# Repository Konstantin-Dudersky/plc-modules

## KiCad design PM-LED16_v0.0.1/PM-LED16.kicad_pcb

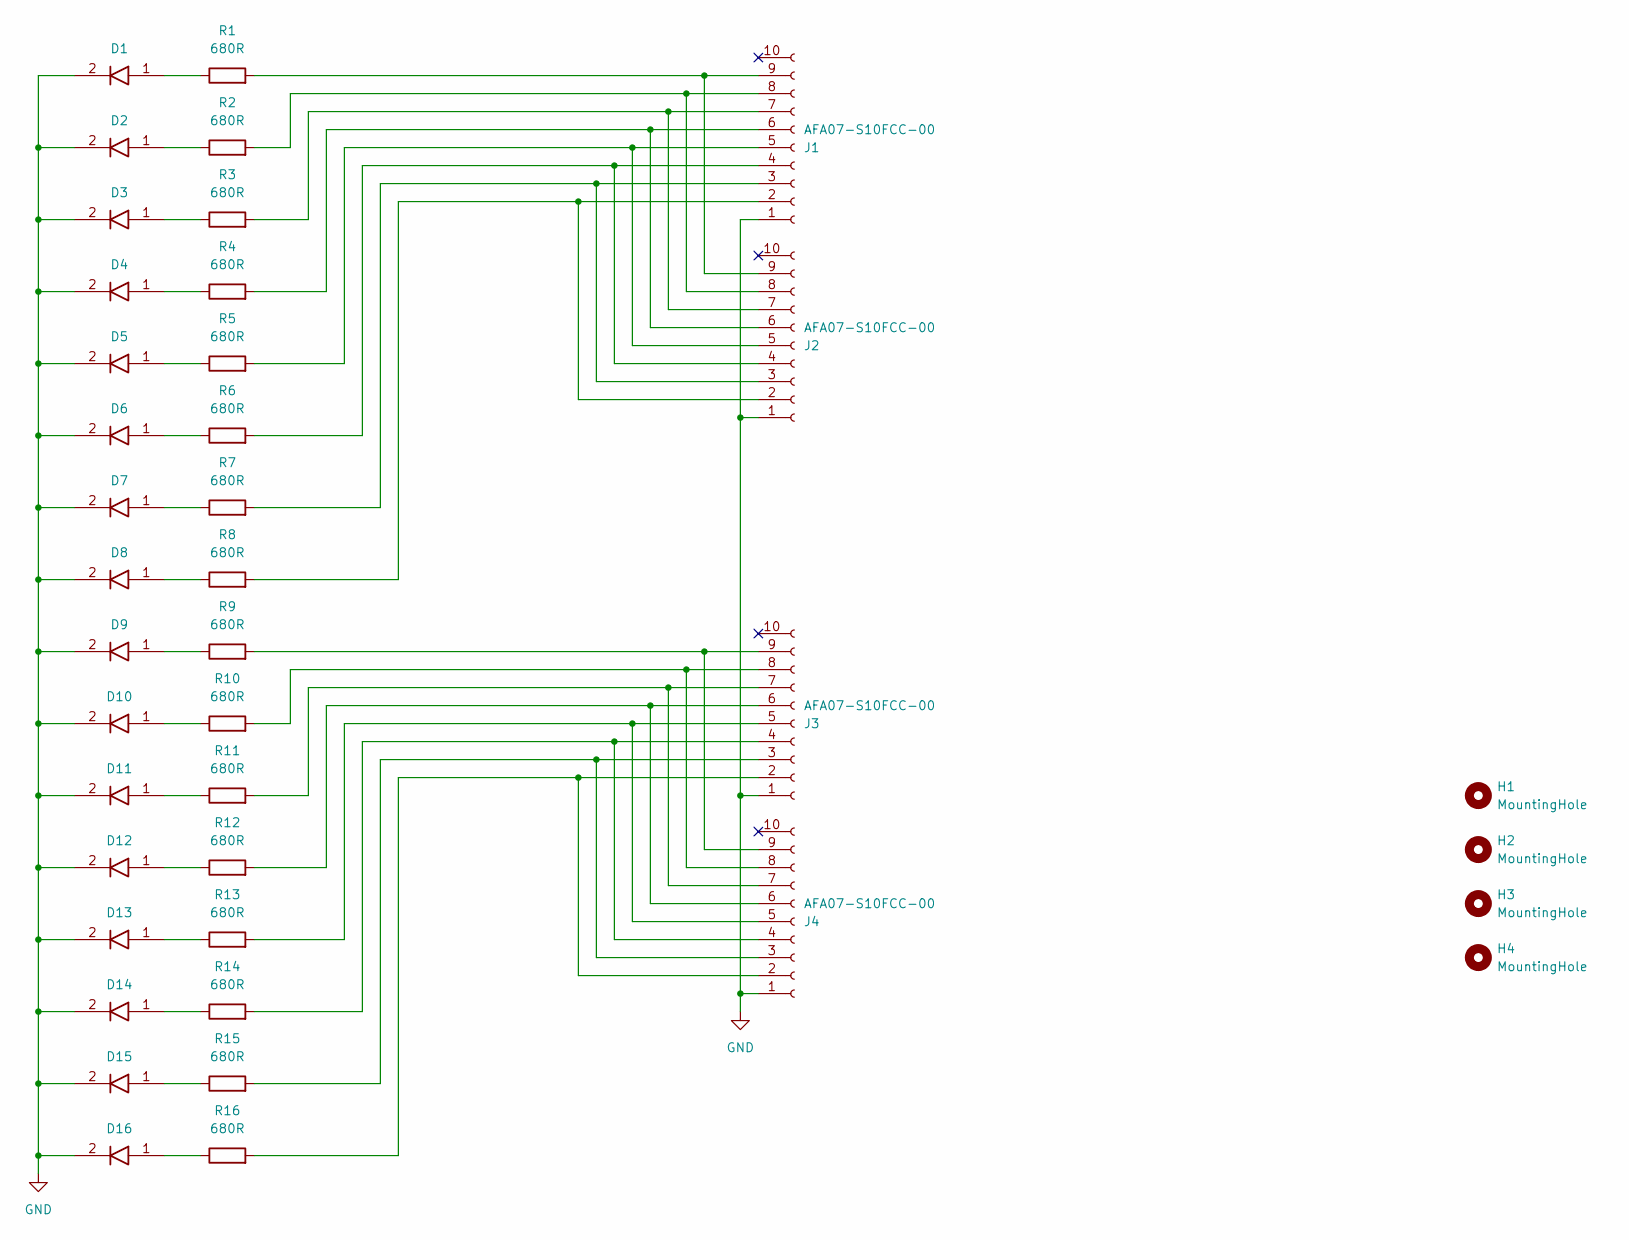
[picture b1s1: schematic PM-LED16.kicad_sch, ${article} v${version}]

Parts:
D1, D2, D3, D4, D5, D6, D7, D8, D9, D10, D11, D12, D13, D14, D15, D16: 12-21_GHC-YR2S2_2C; 1221GHCYR2S22C; part_ipn 12-21/GHC-YR2S2/2C
H1, H2, H3, H4: MountingHole; MountingHole_2.2mm_M2
J1, J2, J3, J4: AFA07-S10FCC-00; CONN10_AFA07-S10_JUS
R1, R2, R3, R4, R5, R6, R7, R8, R9, R10, R11, R12, R13, R14, R15, R16: 680R; R_1206_3216Metric_Pad1.30x1.75mm_HandSolder; part_ipn R_680R_1206_1%

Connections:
GND: D1.2, D2.2, D3.2, D4.2, D5.2, D6.2, D7.2, D8.2, D9.2, D10.2, D11.2, D12.2, D13.2, D14.2, D15.2, D16.2, J1.1, J2.1, J3.1, J4.1
unnamed: D1.1, R1.1
unnamed: D2.1, R2.1
unnamed: D3.1, R3.1
unnamed: D4.1, R4.1
unnamed: D5.1, R5.1
unnamed: D6.1, R6.1
unnamed: D7.1, R7.1
unnamed: D8.1, R8.1
unnamed: D9.1, R9.1
unnamed: D10.1, R10.1
unnamed: D11.1, R11.1
unnamed: D12.1, R12.1
unnamed: D13.1, R13.1
unnamed: D14.1, R14.1
unnamed: D15.1, R15.1
unnamed: D16.1, R16.1
unnamed: J1.2, J2.2, R8.2
unnamed: J1.3, J2.3, R7.2
unnamed: J1.4, J2.4, R6.2
unnamed: J1.5, J2.5, R5.2
unnamed: J1.6, J2.6, R4.2
unnamed: J1.7, J2.7, R3.2
unnamed: J1.8, J2.8, R2.2
unnamed: J1.9, J2.9, R1.2
unnamed: J3.2, J4.2, R16.2
unnamed: J3.3, J4.3, R15.2
unnamed: J3.4, J4.4, R14.2
unnamed: J3.5, J4.5, R13.2
unnamed: J3.6, J4.6, R12.2
unnamed: J3.7, J4.7, R11.2
unnamed: J3.8, J4.8, R10.2
unnamed: J3.9, J4.9, R9.2

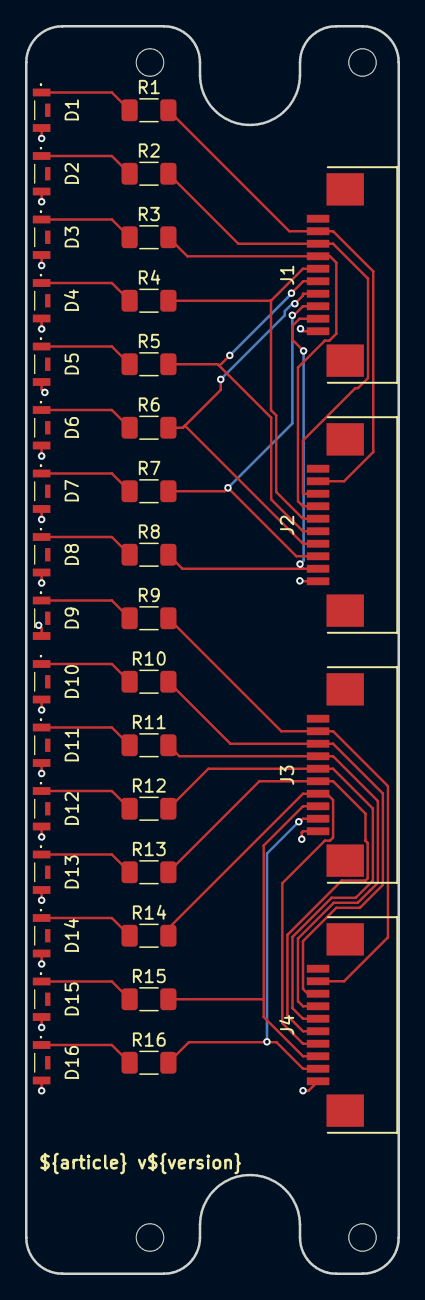
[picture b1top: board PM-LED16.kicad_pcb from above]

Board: 2 copper layers, 29.8 x 99.8 mm, 41 parts (1 on the bottom side), 33 nets.

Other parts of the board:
Logo_kicad: KiCad-Logo2_5mm_SilkScreen

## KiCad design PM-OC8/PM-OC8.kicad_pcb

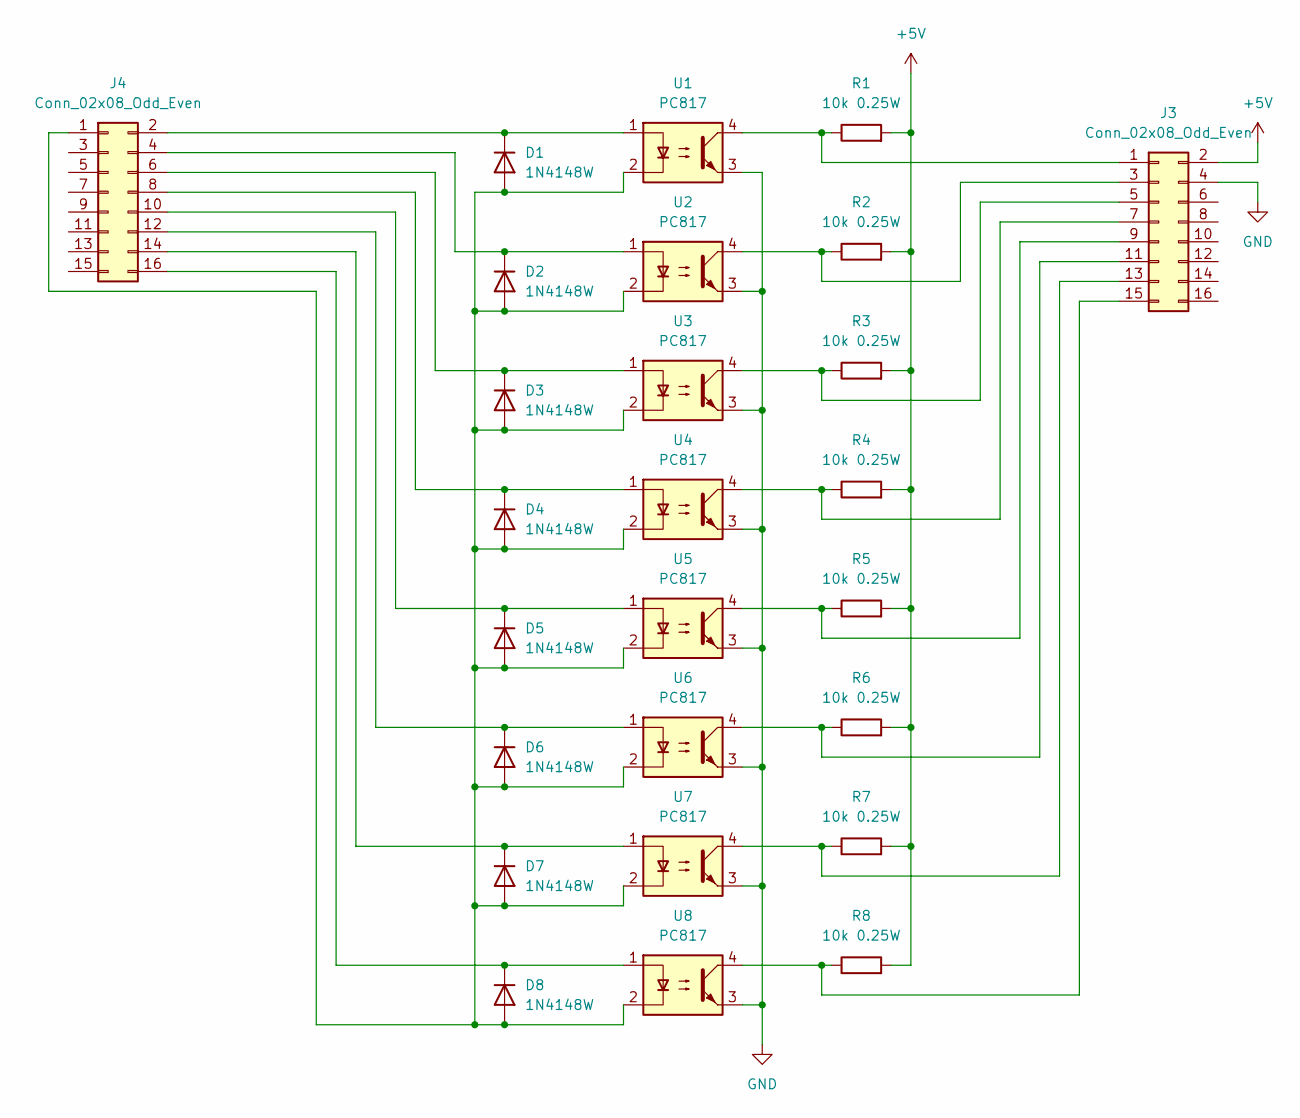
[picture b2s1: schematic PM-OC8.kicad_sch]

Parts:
D1, D2, D3, D4, D5, D6, D7, D8: 1N4148W; D_SOD-123; MfrPart 1N4148W
J3, J4: Conn_02x08_Odd_Even; PinHeader_2x08_P2.54mm_Vertical_SMD
R1, R2, R3, R4, R5, R6, R7, R8: 10k 0.25W; R_1206_3216Metric_Pad1.30x1.75mm_HandSolder
U1, U2, U3, U4, U5, U6, U7, U8: PC817; SOP-4_3.8x4.1mm_P2.54mm

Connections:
+5V: J3.2, R1.2, R2.2, R3.2, R4.2, R5.2, R6.2, R7.2, R8.2
GND: J3.4, U1.3, U2.3, U3.3, U4.3, U5.3, U6.3, U7.3, U8.3
unnamed: D1.2 (A), D2.2 (A), D3.2 (A), D4.2 (A), D5.2 (A), D6.2 (A), D7.2 (A), D8.2 (A), J4.1, U1.2, U2.2, U3.2, U4.2, U5.2, U6.2, U7.2, U8.2
unnamed: D1.1 (K), J4.2, U1.1
unnamed: D2.1 (K), J4.4, U2.1
unnamed: D3.1 (K), J4.6, U3.1
unnamed: D4.1 (K), J4.8, U4.1
unnamed: D5.1 (K), J4.10, U5.1
unnamed: D6.1 (K), J4.12, U6.1
unnamed: D7.1 (K), J4.14, U7.1
unnamed: D8.1 (K), J4.16, U8.1
unnamed: J3.1, R1.1, U1.4
unnamed: J3.3, R2.1, U2.4
unnamed: J3.5, R3.1, U3.4
unnamed: J3.7, R4.1, U4.4
unnamed: J3.9, R5.1, U5.4
unnamed: J3.11, R6.1, U6.4
unnamed: J3.13, R7.1, U7.4
unnamed: J3.15, R8.1, U8.4

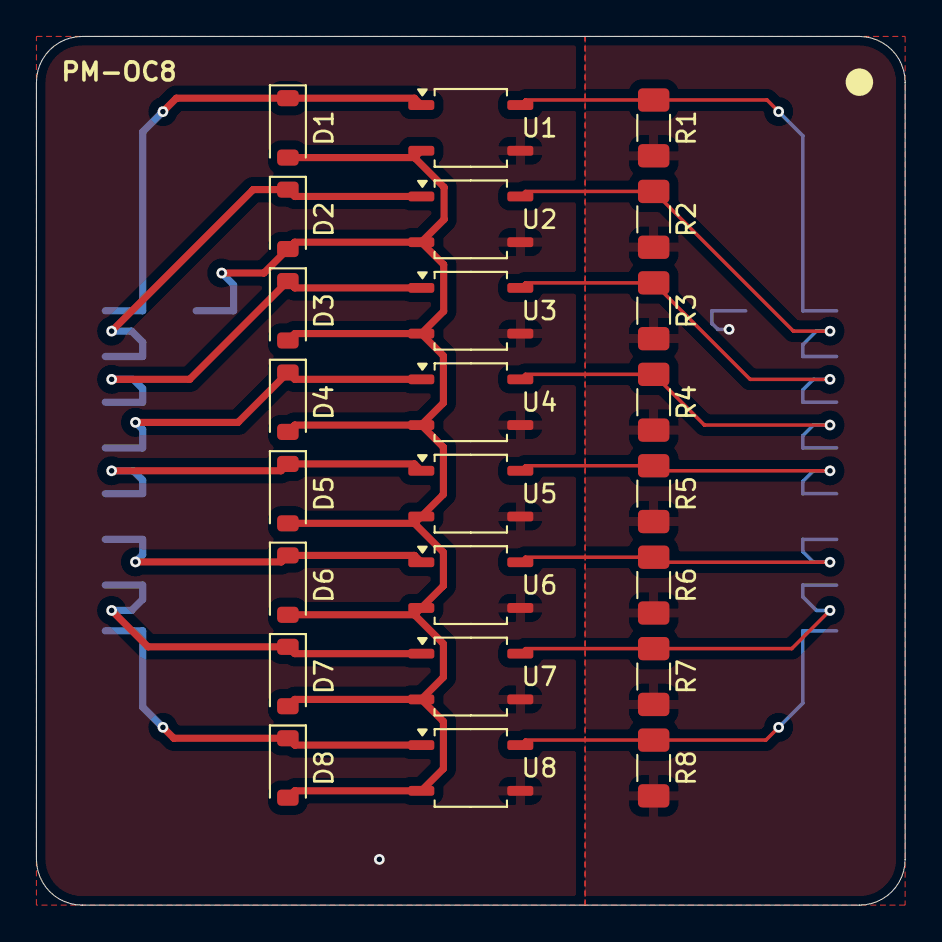
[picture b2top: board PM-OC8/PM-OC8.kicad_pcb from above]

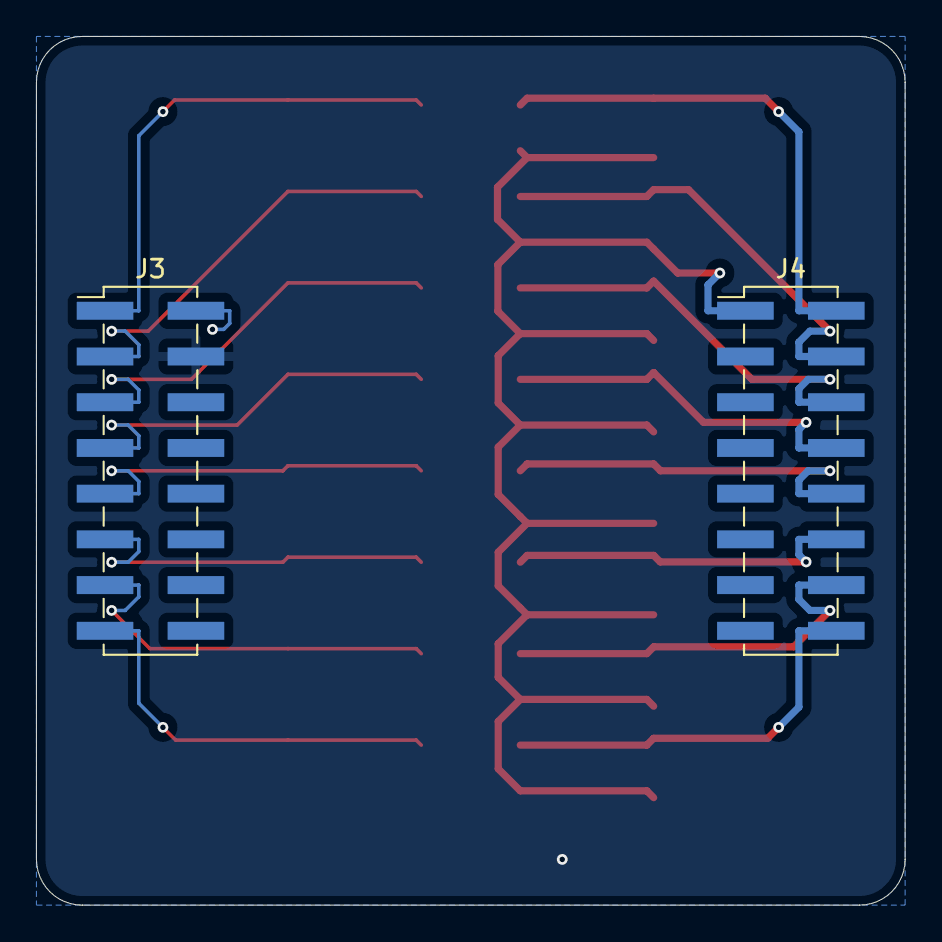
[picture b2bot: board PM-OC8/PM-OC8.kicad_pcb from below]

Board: 2 copper layers, 48.3 x 48.3 mm, 26 parts (2 on the bottom side), 19 nets.

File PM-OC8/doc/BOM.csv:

Reference,Value,Footprint,Qty,NextPCB_price,NextPCB_url
"D1,D2,D3,D4,D5,D6,D7,D8",1N4148W,Diode_SMD:D_SOD-123,8,0.00811,https://www.hqonline.com/product-detail/switching-diodes--sm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
"J3,J4",Conn_02x08_Odd_Even,Connector_PinHeader_2.54mm:PinHeader_2x08_P2.54mm_Vertical_SMD,2,,
"R1,R2,R3,R4,R5,R6,R7,R8",10k 0.25W,Resistor_SMD:R_1206_3216Metric_Pad1.30x1.75mm_HandSolder,8,0.00233,https://www.hqonline.com/product-detail/chip-resistors-yageo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
"U1,U2,U3,U4,U5,U6,U7,U8",PC817,Package_SO:SOP-4_3.8x4.1mm_P2.54mm,8,0.03334,https://www.hqonline.com/product-detail/photocouplers-slkor-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

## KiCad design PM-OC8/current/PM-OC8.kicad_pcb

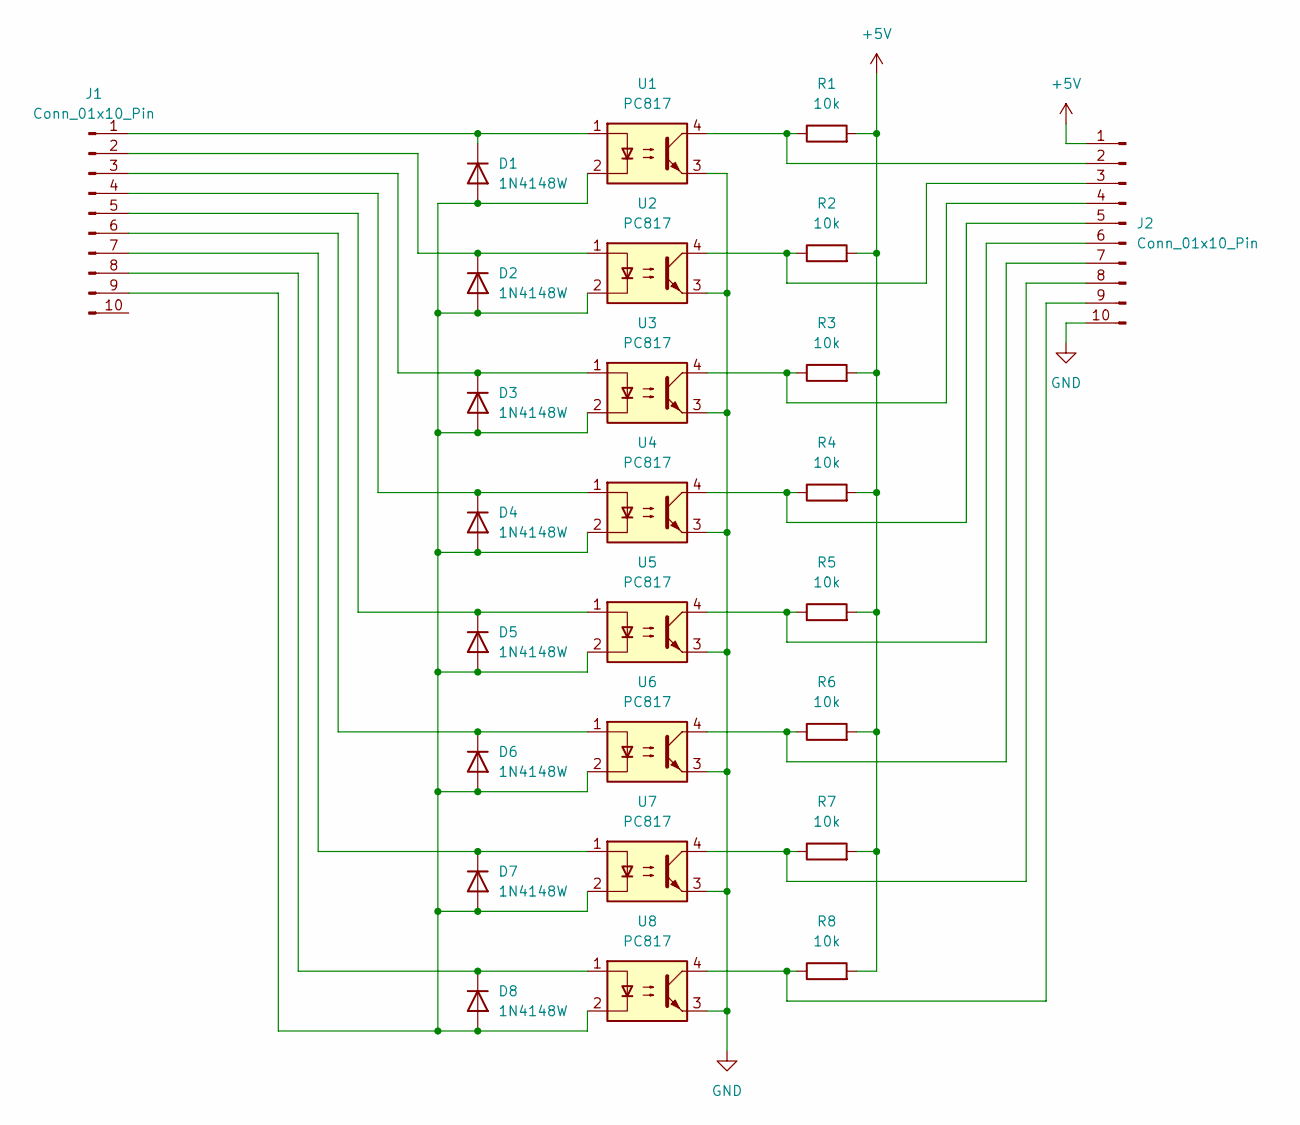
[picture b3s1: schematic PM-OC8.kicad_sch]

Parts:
D1, D2, D3, D4, D5, D6, D7, D8: 1N4148W; D_SOD-123
J1, J2: Conn_01x10_Pin; PinHeader_1x10_P2.54mm_Vertical_SMD_Pin1Left
R1, R2, R3, R4, R5, R6, R7, R8: 10k; R_1206_3216Metric_Pad1.30x1.75mm_HandSolder
U1, U2, U3, U4, U5, U6, U7, U8: PC817; SOP-4_3.8x4.1mm_P2.54mm

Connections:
+5V: J2.1, R1.2, R2.2, R3.2, R4.2, R5.2, R6.2, R7.2, R8.2
GND: J2.10, U1.3, U2.3, U3.3, U4.3, U5.3, U6.3, U7.3, U8.3
unnamed: D1.2 (A), D2.2 (A), D3.2 (A), D4.2 (A), D5.2 (A), D6.2 (A), D7.2 (A), D8.2 (A), J1.9, U1.2, U2.2, U3.2, U4.2, U5.2, U6.2, U7.2, U8.2
unnamed: D1.1 (K), J1.1, U1.1
unnamed: D2.1 (K), J1.2, U2.1
unnamed: D3.1 (K), J1.3, U3.1
unnamed: D4.1 (K), J1.4, U4.1
unnamed: D5.1 (K), J1.5, U5.1
unnamed: D6.1 (K), J1.6, U6.1
unnamed: D7.1 (K), J1.7, U7.1
unnamed: D8.1 (K), J1.8, U8.1
unnamed: J2.2, R1.1, U1.4
unnamed: J2.3, R2.1, U2.4
unnamed: J2.4, R3.1, U3.4
unnamed: J2.5, R4.1, U4.4
unnamed: J2.6, R5.1, U5.4
unnamed: J2.7, R6.1, U6.4
unnamed: J2.8, R7.1, U7.4
unnamed: J2.9, R8.1, U8.4

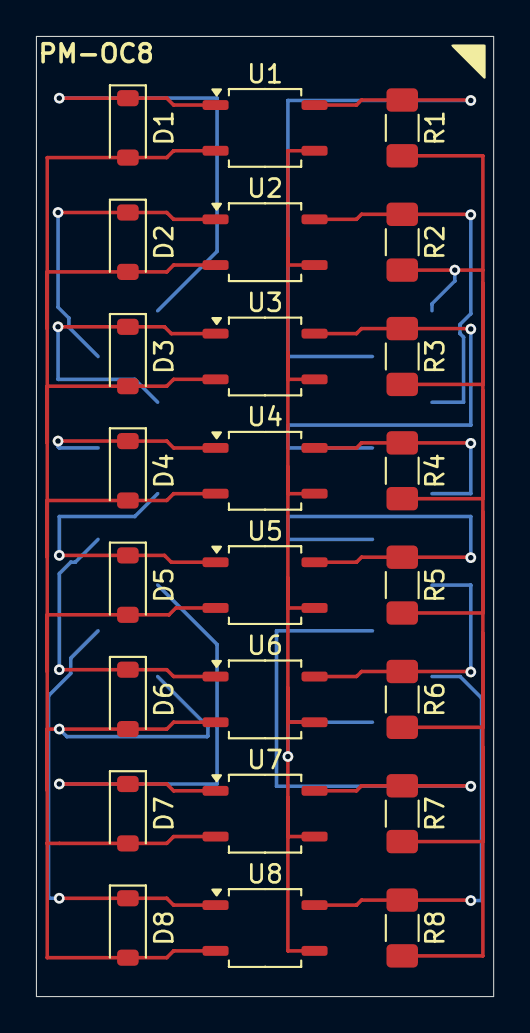
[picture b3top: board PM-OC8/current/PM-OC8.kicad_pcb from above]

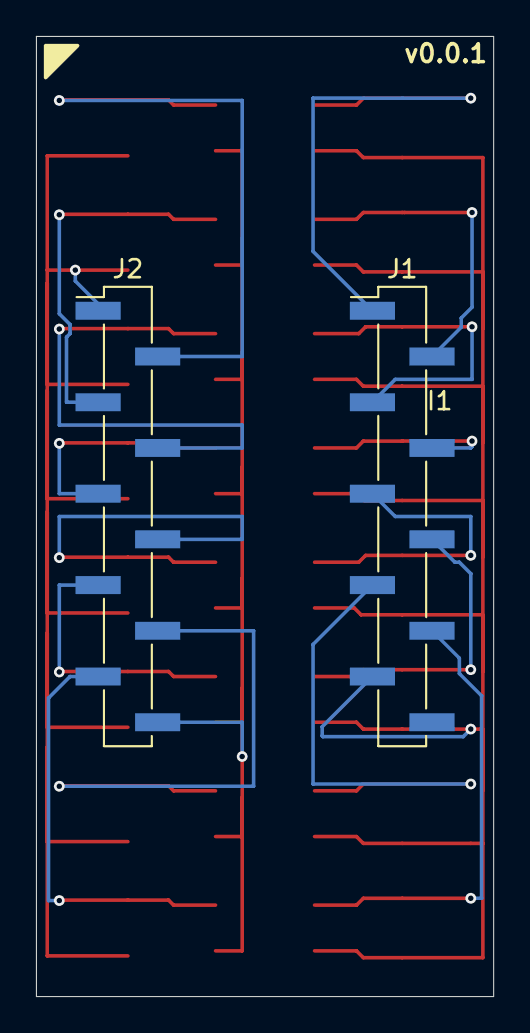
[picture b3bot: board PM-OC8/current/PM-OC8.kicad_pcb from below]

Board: 2 copper layers, 25.4 x 53.3 mm, 26 parts (2 on the bottom side), 19 nets.

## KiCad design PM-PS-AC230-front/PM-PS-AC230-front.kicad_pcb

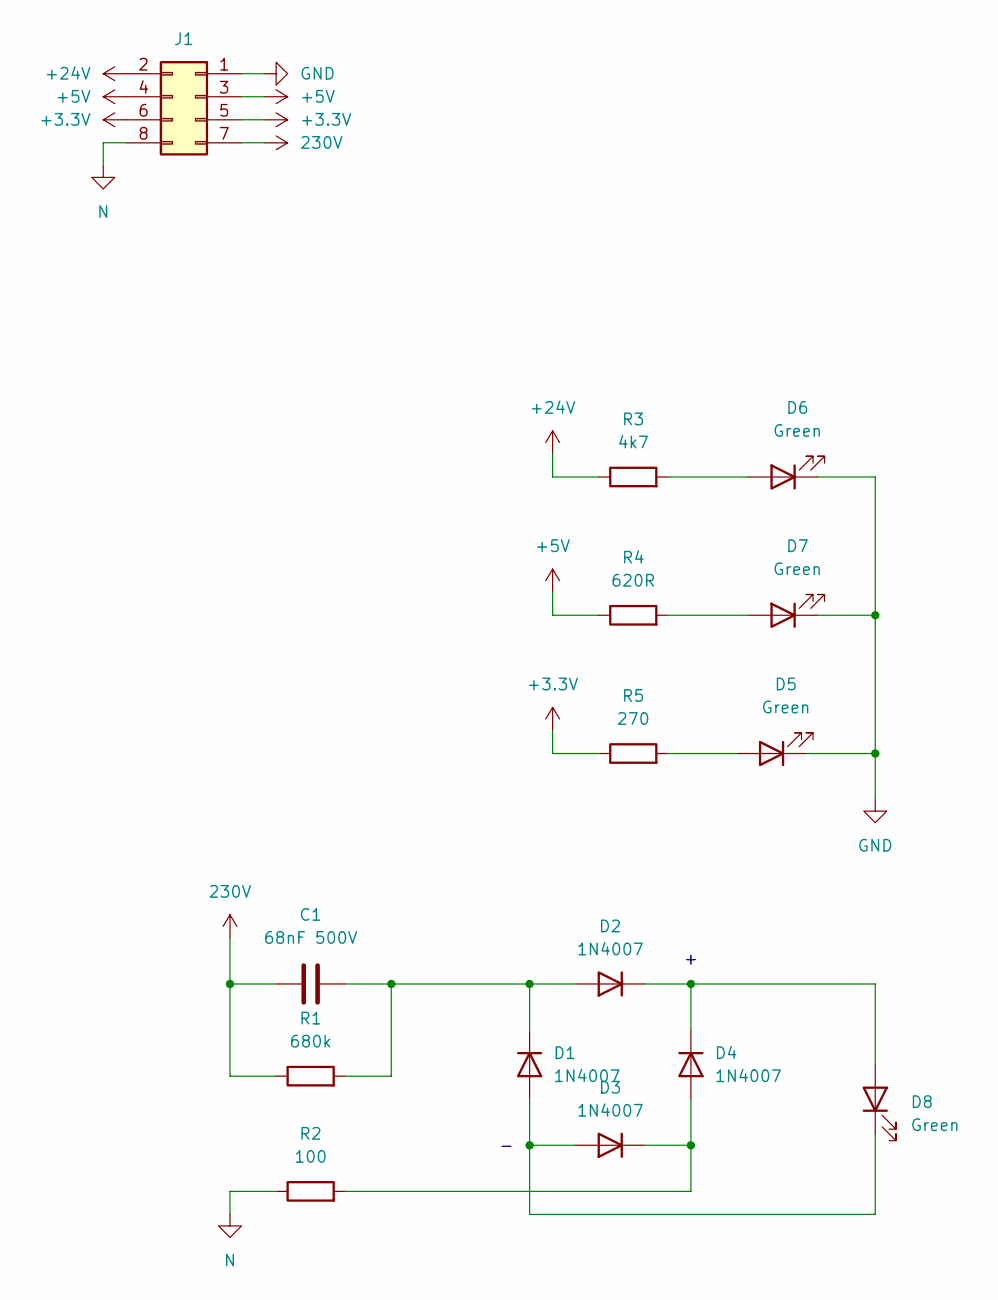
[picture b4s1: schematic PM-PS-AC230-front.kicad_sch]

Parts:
C1: 68nF 500V; C_1210_3225Metric_Pad1.33x2.70mm_HandSolder; part_ipn C_68nF_500V_1210
D1, D2, D3, D4: 1N4007; D_SMA; part_ipn 1N4007
D5, D6, D7, D8: Green; LED_1206_3216Metric_ReverseMount_Hole1.8x2.4mm; part_ipn LED_green_1206_reverse
J1: PinHeader_02x04_P2.54_THT_angle; PinHeader_2x04_P2.54mm_Horizontal; part_ipn PinHeader_02x04_P2.54_THT_angle
R1: 680k; R_1206_3216Metric_Pad1.30x1.75mm_HandSolder; part_ipn R_680k_1206_1%
R2: 100; R_1206_3216Metric_Pad1.30x1.75mm_HandSolder; part_ipn R_100_1206_1%
R3: 4k7; R_1206_3216Metric_Pad1.30x1.75mm_HandSolder; part_ipn R_4k7_1206_1%
R4: 620R; R_1206_3216Metric_Pad1.30x1.75mm_HandSolder; part_ipn R_620R_1206_1%
R5: 270; R_1206_3216Metric_Pad1.30x1.75mm_HandSolder; part_ipn R_270_1206_1%

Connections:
230V: C1.1, J1.7, R1.1
+3.3V: J1.5, J1.6, R5.1
+5V: J1.3, J1.4, R4.1
+24V: J1.2, R3.1
GND: D5.1 (K), D6.1 (K), D7.1 (K), J1.1
N: J1.8, R2.1
unnamed: D1.2 (A), D3.2 (A), D8.1 (K)
unnamed: C1.2, D1.1 (K), D2.2 (A), R1.2
unnamed: D2.1 (K), D4.1 (K), D8.2 (A)
unnamed: D3.1 (K), D4.2 (A), R2.2
unnamed: D5.2 (A), R5.2
unnamed: D6.2 (A), R3.2
unnamed: D7.2 (A), R4.2

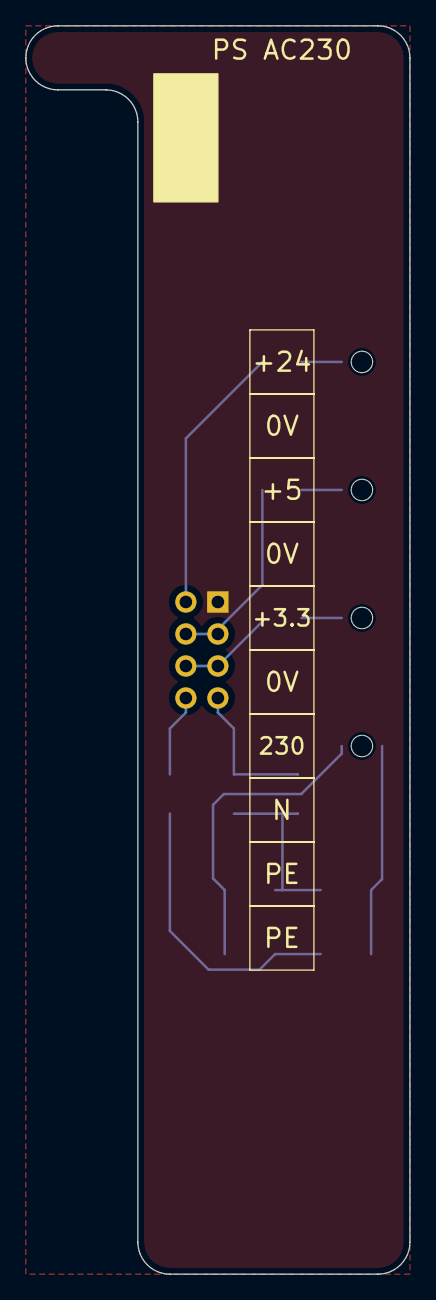
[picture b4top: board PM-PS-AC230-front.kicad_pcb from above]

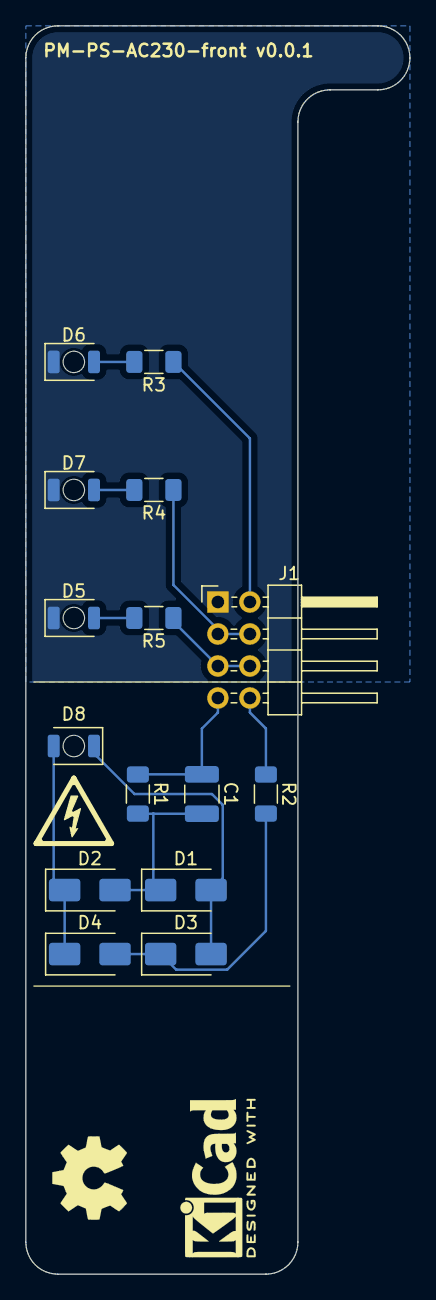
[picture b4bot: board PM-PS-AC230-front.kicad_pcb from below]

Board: 2 copper layers, 30.5 x 99.1 mm, 17 parts (17 on the bottom side), 13 nets.

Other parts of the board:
Logo_kicad: KiCad-Logo2_5mm_SilkScreen
logo_high_voltage: symbol_high_voltage
